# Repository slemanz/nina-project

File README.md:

# NINA Project

## Overview

The NINA Project was developed to create a data acquisition device. This project is structured into two main directories: **hardware** and **firmware**.
Each section contains essential components for building and programming the device.

### Directories

- **[HARDWARE](HW/)**: Contains the hardware specifications and schematics.
- **[FIRMWARE](FW/)**: Contains the low-level driver implementations and application structure.

For further details, please refer to the specific READMEs in their respective directories.

## Versions

**v1.0** - First stable version. This release was officially utilized as the
technical foundation for the repository owner's Undergraduate Graduation Thesis
(TCC).

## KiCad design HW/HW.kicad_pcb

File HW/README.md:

# Hardware

## Overview

In the hardware directory, have been designed a simple conception board for the data acquisition device. The design encompasses basic electronic components
meeded.

### Schematic

You can find the schematic for the hardware [here](Schematic/HW.pdf).

This schematic illustrates the connections and components used for this project. Feel free to explore and modify it as per your requirements.

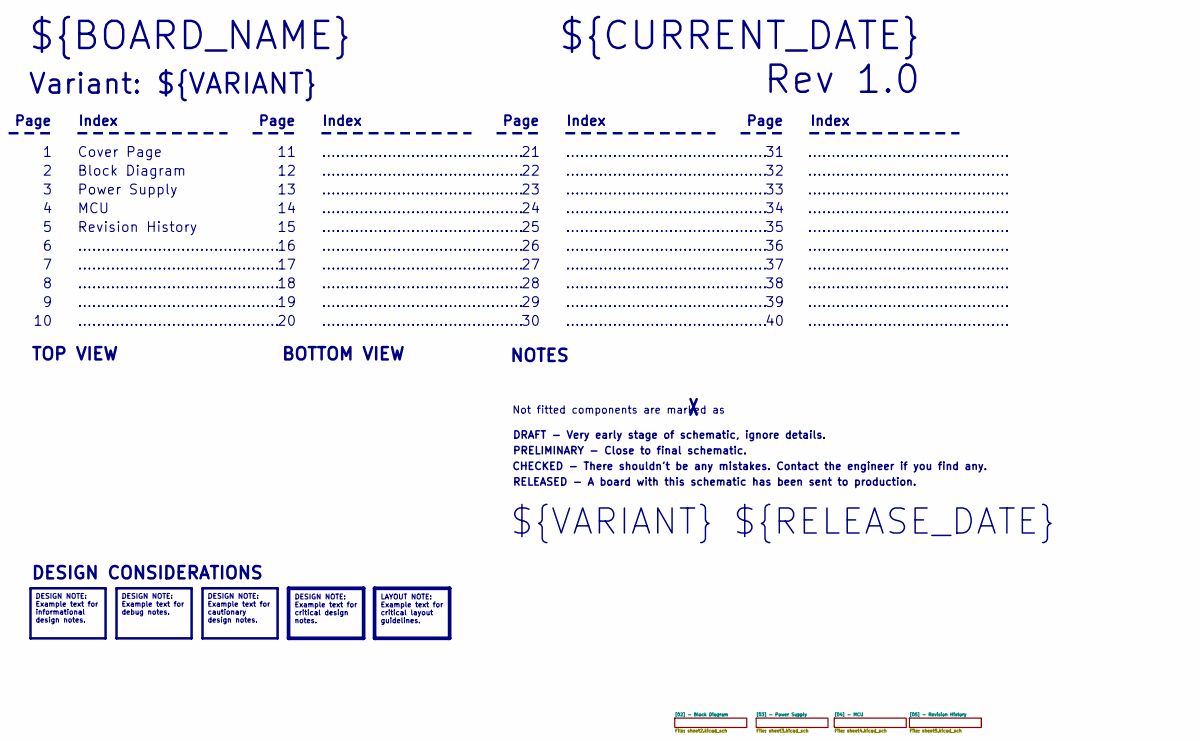
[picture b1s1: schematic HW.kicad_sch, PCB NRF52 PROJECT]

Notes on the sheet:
...........................................
DRAFT - Very early stage of schematic, ignore details.
Index
Page
Cover Page
MCU
Revision History
TOP VIEW
CHECKED - There shouldn't be any mistakes. Contact the engineer if you find any.
DESIGN CONSIDERATIONS
Block Diagram
BOTTOM VIEW
${CURRENT_DATE}
NOTES
Not fitted components are marked as
PRELIMINARY - Close to final schematic.
Variant: ${VARIANT}
Power Supply
RELEASED - A board with this schematic has been sent to production.
${BOARD_NAME}
Rev ${REVISION}
${VARIANT} ${RELEASE_DATE}
DESIGN NOTE: Example text for informational design notes.
DESIGN NOTE: Example text for critical design notes.
LAYOUT NOTE: Example text for critical layout guidelines.
DESIGN NOTE: Example text for cautionary design notes.
DESIGN NOTE: Example text for debug notes.

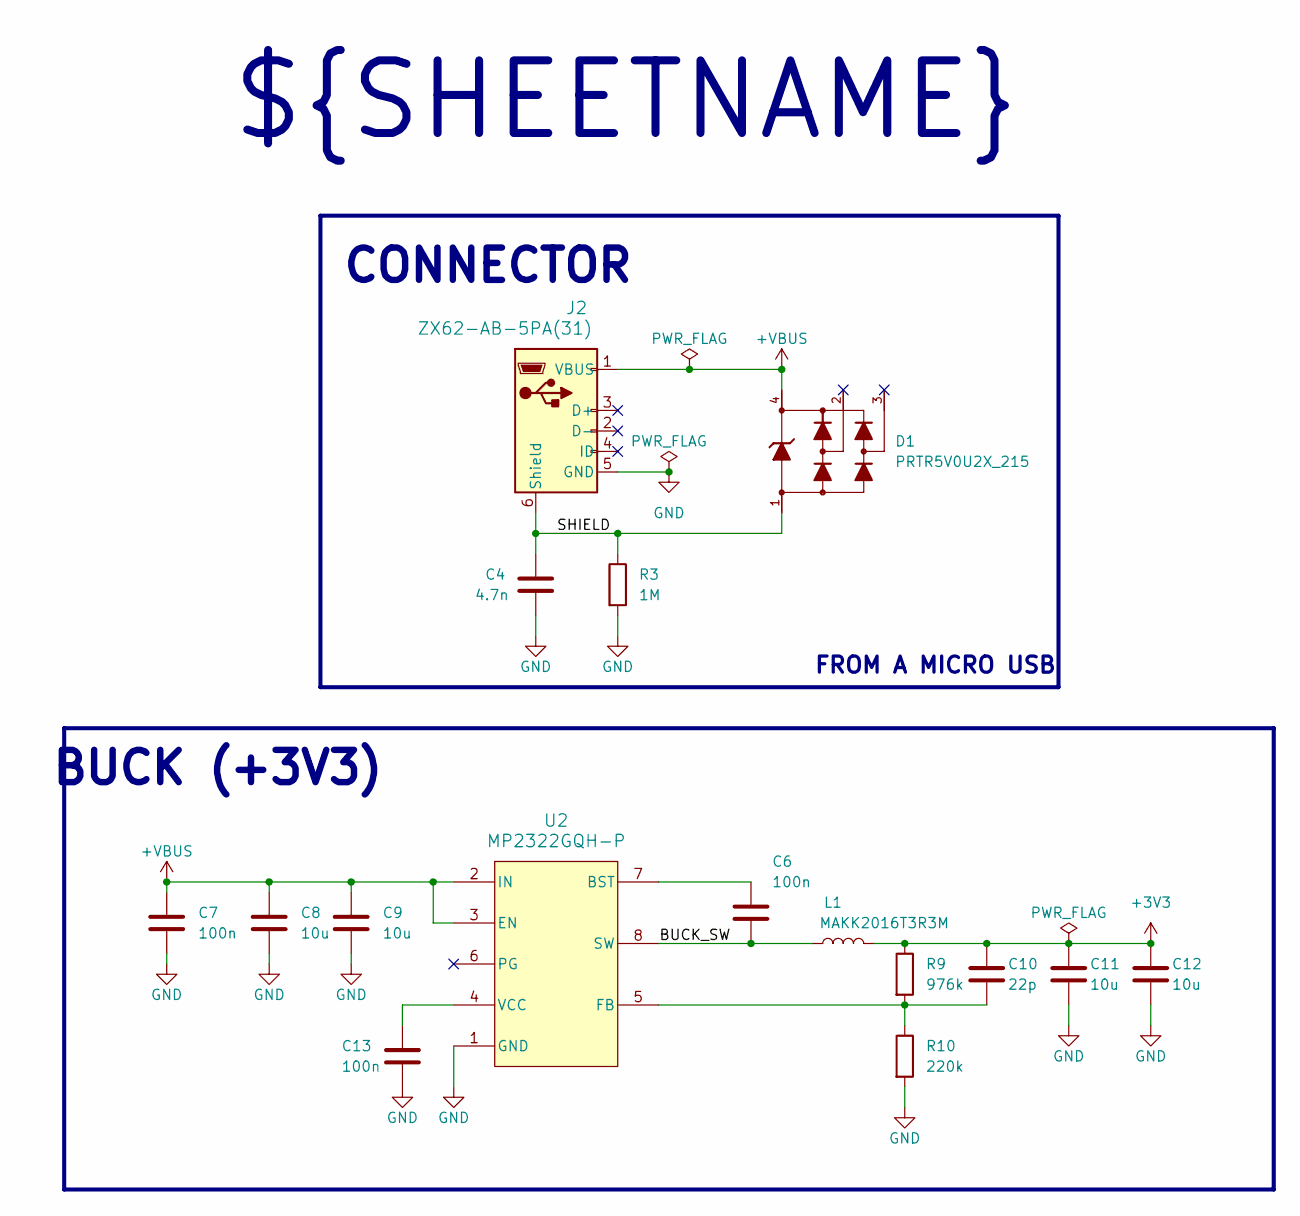
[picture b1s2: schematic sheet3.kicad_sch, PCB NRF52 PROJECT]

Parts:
C4: 4.7n; C_0805_2012Metric
C6, C7, C13: 100n; C_0402_1005Metric
C8, C9, C11, C12: 10u; C_0603_1608Metric
C10: 22p; C_0402_1005Metric
D1: PRTR5V0U2X_215; SOT143B
J2: ZX62-AB-5PA(31); CONN5_ZX62-AB-5PA_HIR
L1: MAKK2016T3R3M; INDC2016X100N
R3: 1M; R_0402_1005Metric
R9: 976k; R_0402_1005Metric
R10: 220k; R_0402_1005Metric
U2: MP2322GQH-P; QFN-8_1p5MMx2MM_MNP

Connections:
+3V3: C10.1, C11.1, C12.1, L1.2, R9.1; also elsewhere on the board
+VBUS: C7.1, C8.1, C9.1, D1.4, J2.1 (VBUS), U2.2 (IN), U2.3 (EN); also elsewhere on the board
/[03] - Power Supply/BUCK_SW: C6.2, L1.1, U2.8 (SW)
/[03] - Power Supply/SHIELD: C4.1, D1.1, J2.6 (Shield), J2.7 (Shield), J2.8 (Shield), J2.9 (Shield), R3.1
GND: C4.2, C7.2, C8.2, C9.2, C11.2, C12.2, C13.2, J2.5 (GND), R3.2, R10.2, U2.1 (GND); also elsewhere on the board
unnamed: C6.1, U2.7 (BST)
unnamed: C10.2, R9.2, R10.1, U2.5 (FB)
unnamed: C13.1, U2.4 (VCC)

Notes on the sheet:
BUCK (+3V3)
CONNECTOR
FROM A MICRO USB
${SHEETNAME}

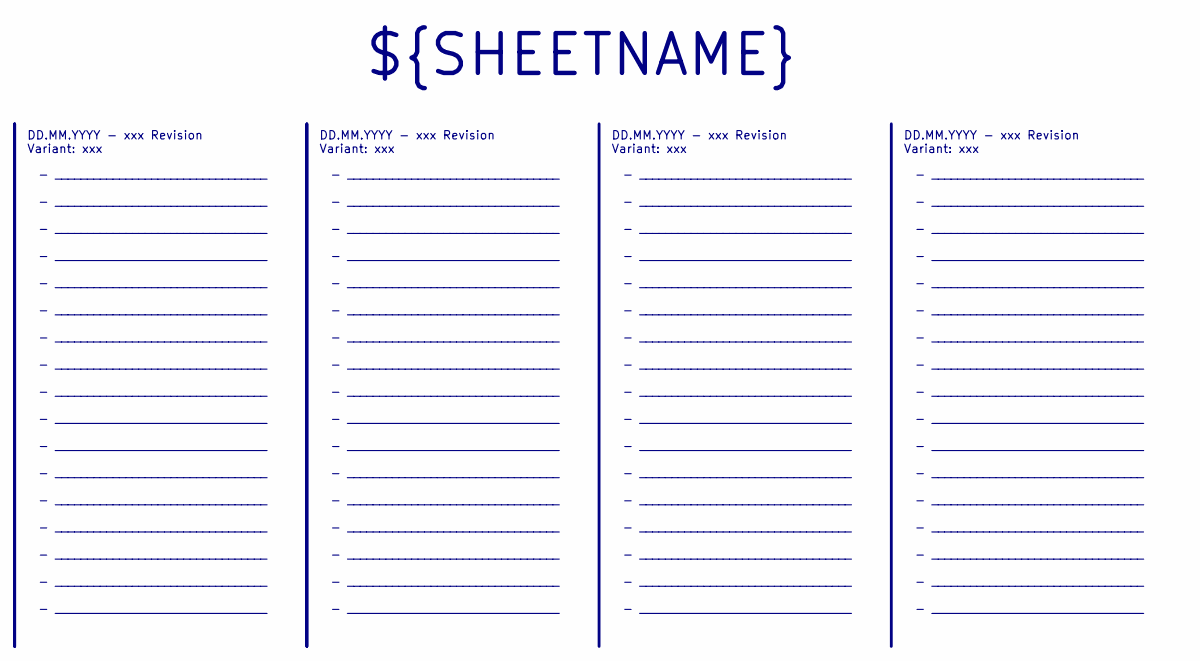
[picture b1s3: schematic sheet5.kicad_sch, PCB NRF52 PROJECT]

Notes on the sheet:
${SHEETNAME}
DD.MM.YYYY - xxx Revision Variant: xxx
- _________________________________ - _________________________________ - _________________________________ - _________________________________ - _________________________________ - _________________________________ - _________________________________ - _________________________________ - _________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

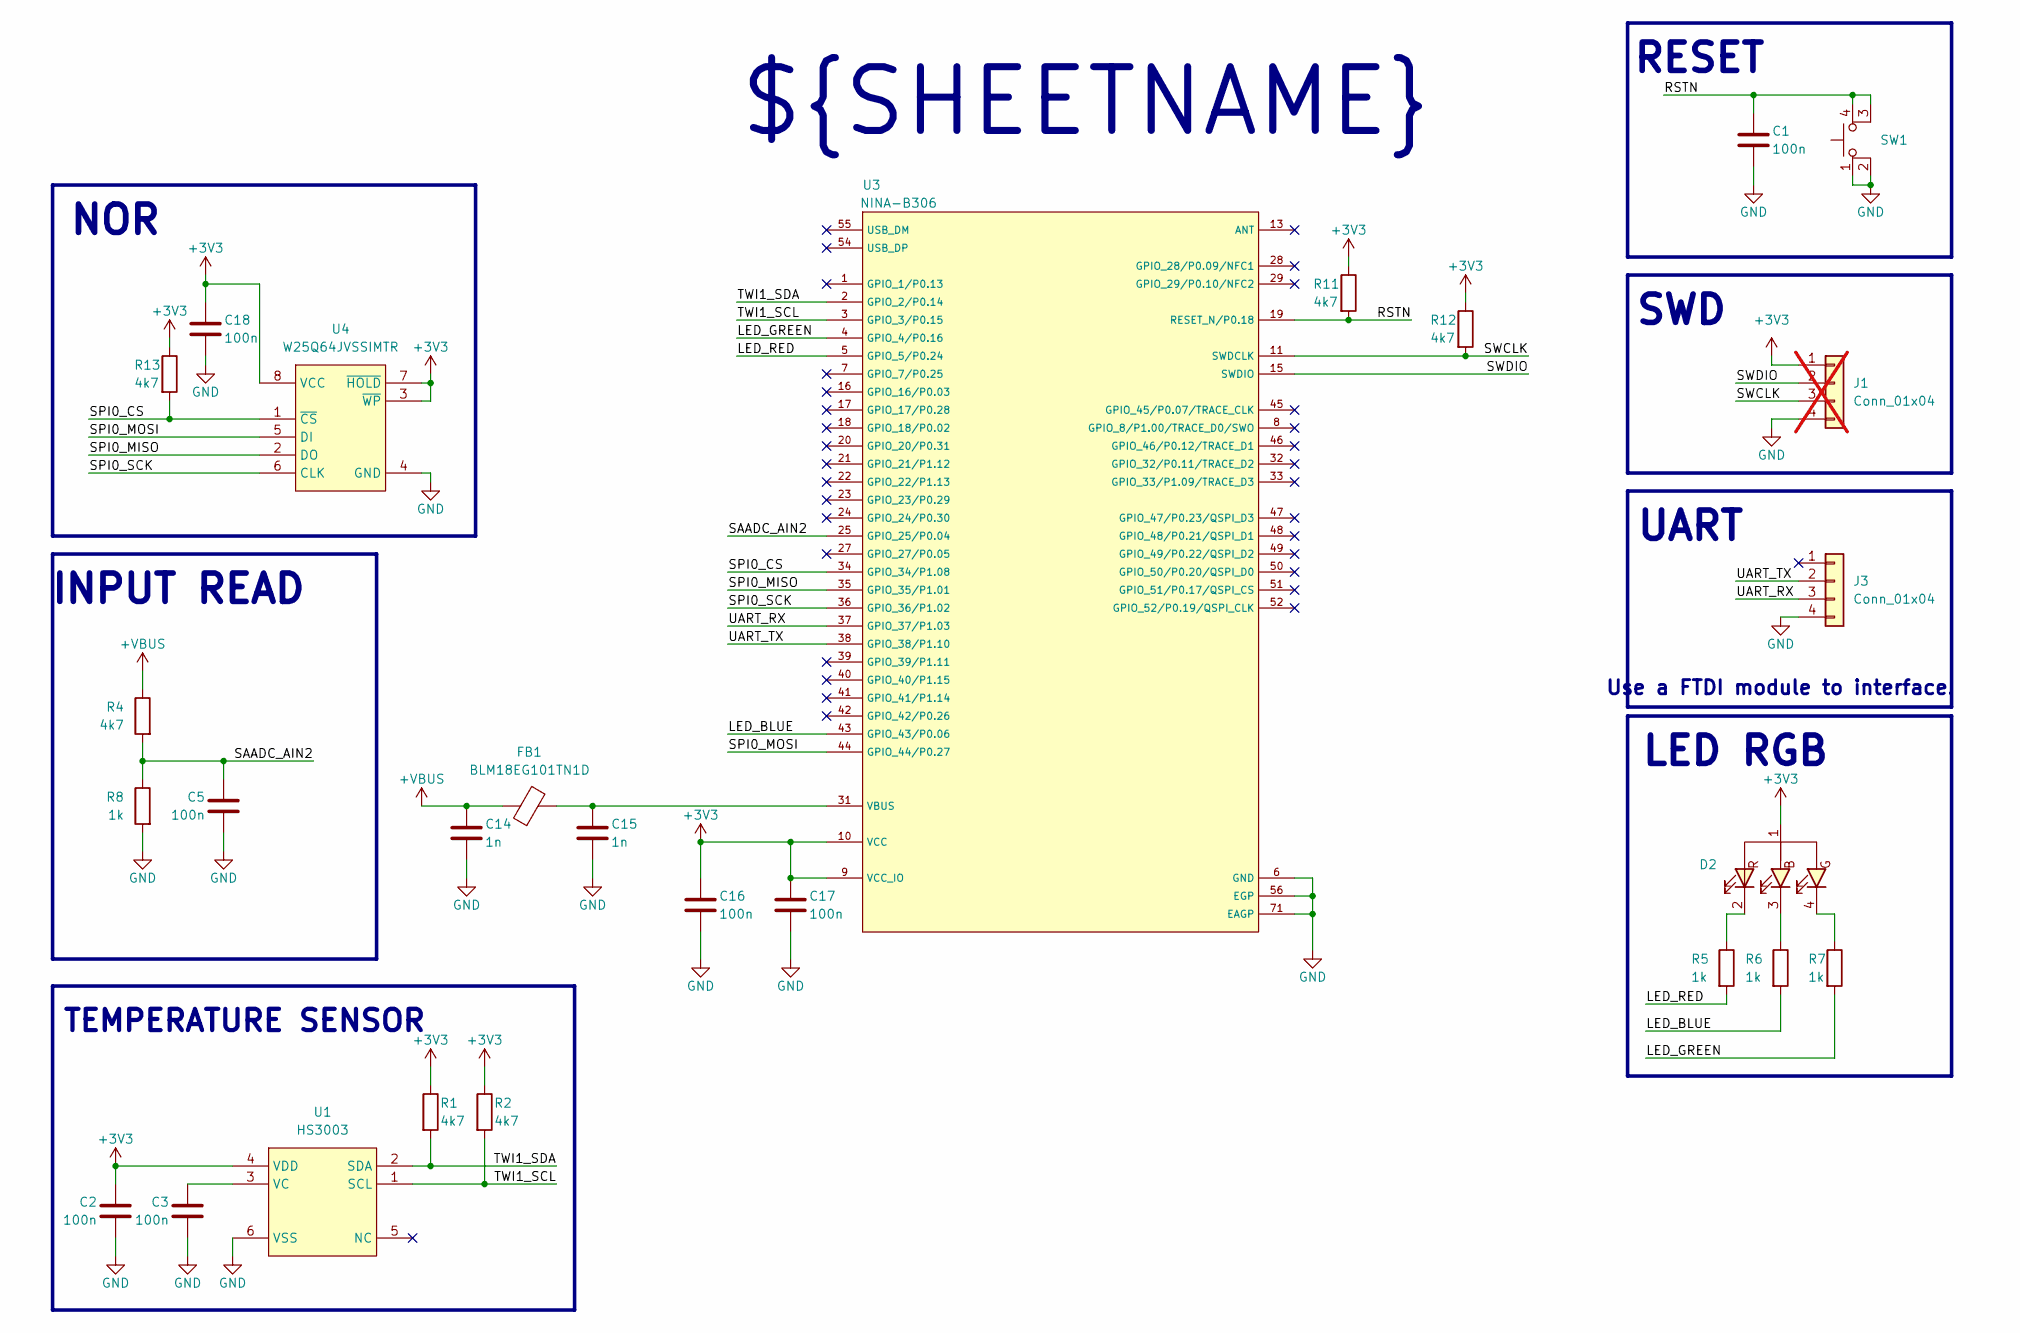
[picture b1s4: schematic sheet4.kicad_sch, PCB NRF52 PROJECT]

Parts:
C1, C2, C3, C5, C16, C17, C18: 100n; C_0402_1005Metric
C14, C15: 1n; C_0402_1005Metric
D2: LED_SML-P24M_ROM
FB1: BLM18EG101TN1D; L_0603_1608Metric
J1: Conn_01x04; PinHeader_1x04_P2.54mm_Vertical; not fitted
J3: Conn_01x04; MOLEX_530480410
R1, R2, R4, R11, R12, R13: 4k7; R_0402_1005Metric
R5, R6, R7, R8: 1k; R_0402_1005Metric
SW1: PTS526SK15SMTR2LFS; SW-SMD_4P-L5.2-W5.2-P3.70-LS6.4; LCSC C2689521
U1: HS3003; XDCR_HS3003
U3: NINA-B306; NINA_LGA71R_1500X1000X223_PCB
U4: W25Q64JVSSIMTR; SOIC-8_5.3x5.3mm_P1.27mm

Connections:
+3V3: C2.1, C16.1, C17.1, C18.1, D2.1, J1.1, R1.1, R2.1, R11.1, R12.1, R13.1, U1.4 (VDD), U3.9 (VCC_IO), U3.10 (VCC), U4.3 (~WP), U4.7 (~HOLD), U4.8 (VCC); also elsewhere on the board
+VBUS: C14.1, FB1.1, R4.1; also elsewhere on the board
/[04] - MCU/LED_BLUE: R6.2, U3.43 (GPIO_43/P0.06)
/[04] - MCU/LED_GREEN: R7.2, U3.4 (GPIO_4/P0.16)
/[04] - MCU/LED_RED: R5.2, U3.5 (GPIO_5/P0.24)
/[04] - MCU/RSTN: C1.1, R11.2, SW1.3, SW1.4, U3.19 (RESET_N/P0.18)
/[04] - MCU/SAADC_AIN2: C5.1, R4.2, R8.1, U3.25 (GPIO_25/P0.04)
/[04] - MCU/SPI0_CS: R13.2, U3.34 (GPIO_34/P1.08), U4.1 (~CS)
/[04] - MCU/SPI0_MISO: U3.35 (GPIO_35/P1.01), U4.2 (DO)
/[04] - MCU/SPI0_MOSI: U3.44 (GPIO_44/P0.27), U4.5 (DI)
/[04] - MCU/SPI0_SCK: U3.36 (GPIO_36/P1.02), U4.6 (CLK)
/[04] - MCU/SWCLK: J1.3, R12.2, U3.11 (SWDCLK)
/[04] - MCU/SWDIO: J1.2, U3.15 (SWDIO)
/[04] - MCU/TWI1_SCL: R2.2, U1.1 (SCL), U3.3 (GPIO_3/P0.15)
/[04] - MCU/TWI1_SDA: R1.2, U1.2 (SDA), U3.2 (GPIO_2/P0.14)
/[04] - MCU/UART_RX: J3.3, U3.37 (GPIO_37/P1.03)
/[04] - MCU/UART_TX: J3.2, U3.38 (GPIO_38/P1.10)
GND: C1.2, C2.2, C3.2, C5.2, C14.2, C15.2, C16.2, C17.2, C18.2, J1.4, J3.4, R8.2, SW1.1, SW1.2, U1.6 (VSS), U3.6 (GND), U3.12 (GND), U3.14 (GND), U3.26 (GND), U3.30 (GND), U3.53 (GND), U3.56 (EGP), U3.57 (EGP), U3.58 (EGP), U3.59 (EGP), U3.60 (EGP), U3.61 (EGP), U3.62 (EGP), U3.63 (EGP), U3.64 (EGP), U3.65 (EGP), U3.66 (EGP), U3.67 (EGP), U3.68 (EAGP), U3.69 (EAGP), U3.70 (EAGP), U3.71 (EAGP), U4.4 (GND); also elsewhere on the board
unnamed: D2.2, R5.1
unnamed: D2.3, R6.1
unnamed: D2.4, R7.1
unnamed: C3.1, U1.3 (VC)
unnamed: C15.1, FB1.2, U3.31 (VBUS)

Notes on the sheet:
TEMPERATURE SENSOR
NOR
LED RGB
SWD
UART
${SHEETNAME}
Use a FTDI module to interface.
RESET
INPUT READ

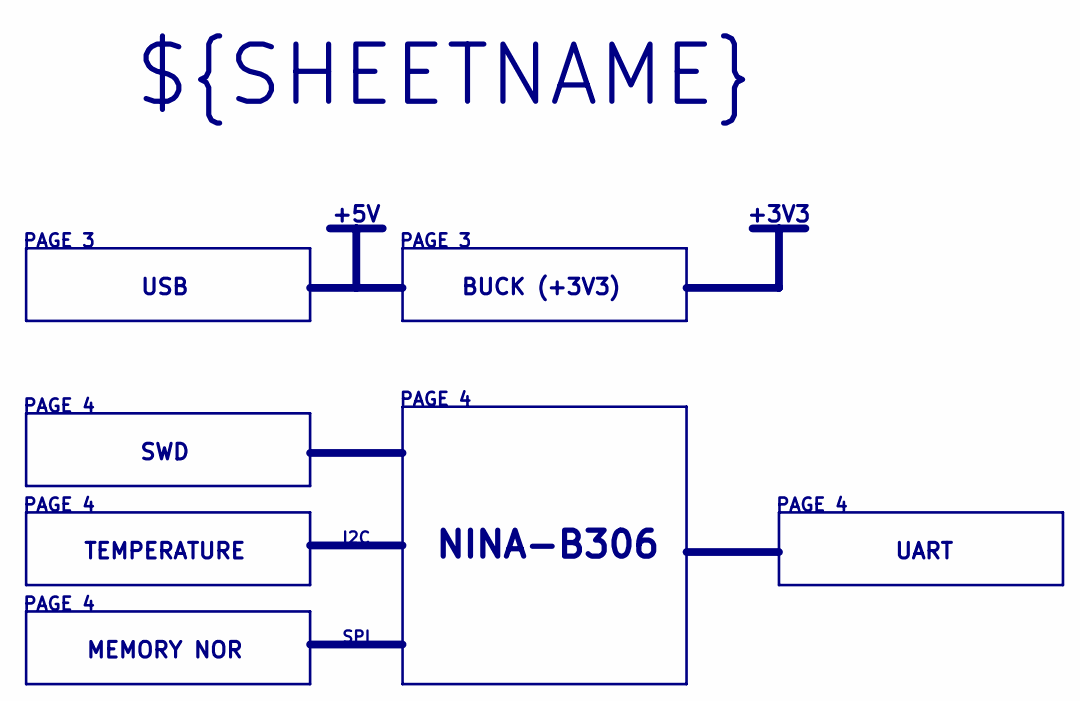
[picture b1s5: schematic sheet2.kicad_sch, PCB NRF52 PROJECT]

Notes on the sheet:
UART
+5V
BUCK (+3V3)
PAGE 4
SWD
PAGE 3
MEMORY NOR
NINA-B306
I2C
USB
SPI
${SHEETNAME}
+3V3
TEMPERATURE

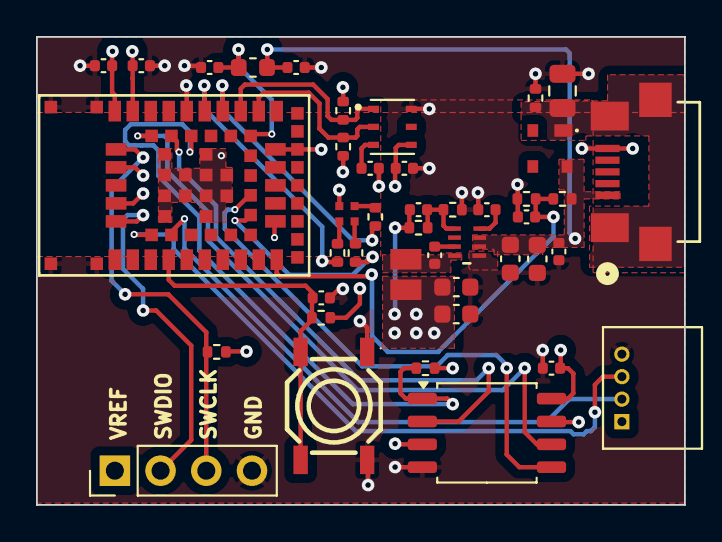
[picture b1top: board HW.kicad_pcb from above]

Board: 4 copper layers, 36.0 x 26.0 mm, 43 parts (0 on the bottom side), 28 nets.

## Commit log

2025-05-25 project(feat): change gitignore
2025-05-25 project(feat): add hw lib
2025-05-26 project(feat): add kicad HW project
2025-05-26 project(feat): add schematic project
2025-05-27 project(feat): add footprint table
2025-05-27 project(feat): add symbol table
2025-05-28 project(feat): add sheet2
2025-05-28 project(feat): add sheet3
2025-06-01 project(feat): add sheet4
2025-06-02 project(feat): add sheet5
2025-06-03 project(feat): add pcb project
2025-06-07 project(feat): add schematic in pdf
2025-06-07 project(feat): add 3d images from board
2025-06-10 project(feat): improve main readme
2025-06-10 project(change): move makefile and generate new bin file
2025-06-11 project(feat): add image to main readme
2025-06-16 project(feat): improve FW readme
2025-06-17 project(feat): add hardware readme
2026-01-06 HW(feat): change schematic to checked
2026-01-06 v1.0
